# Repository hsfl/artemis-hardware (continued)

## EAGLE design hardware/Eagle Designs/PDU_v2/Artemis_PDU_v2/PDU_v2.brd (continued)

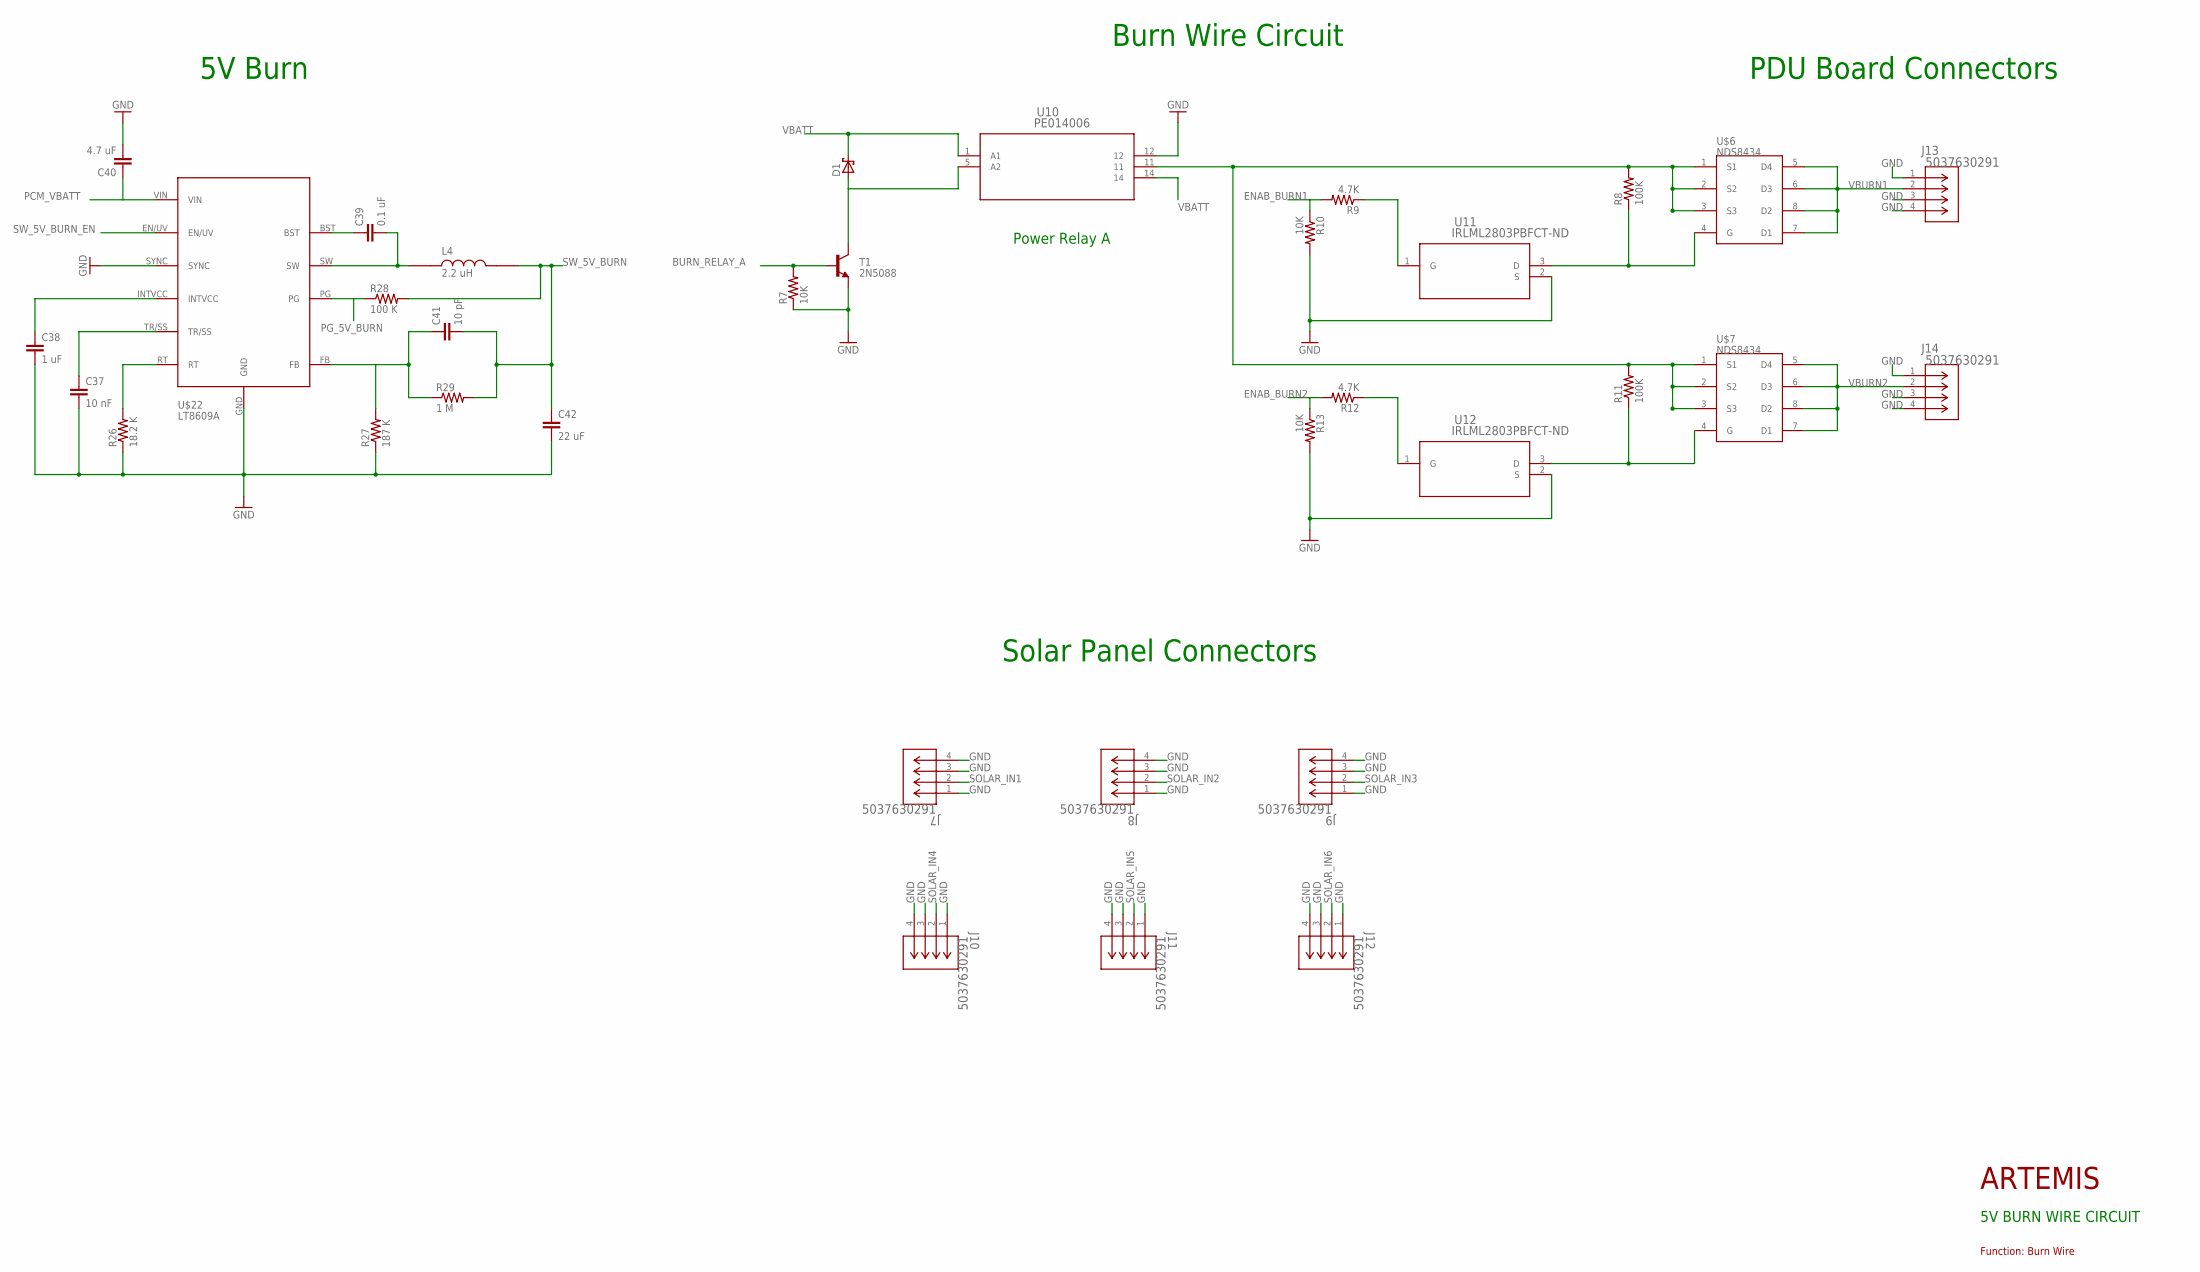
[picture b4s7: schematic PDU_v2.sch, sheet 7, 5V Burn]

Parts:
C37: 10 nF; 0805
C38: 1 uF; 0805
C39: 0.1 uF; 0805
C40: 4.7 uF; 0805
C41: 10 pF; 0805
C42: 22 uF; 1206
D1: SBR2A40P1Q7DFLS130L-7; POWERDI-123
J7, J8, J9, J10, J11, J12, J13, J14: 5037630291; CON_5037630291
L4: 2.2 uH; IND_XFL4020-222ME
R7, R10, R13: 10K; 0603-RES
R8, R11: 100K; 0603-RES
R9, R12: 4.7K; 0603-RES
R26: 18.2 K; 0805
R27: 187 K; 0805
R28: 100 K; 0805
R29: 1 M; 0805
T1: 2N5088; TO92
U10: PE014006; RELAY5-PE_CO
U11, U12: IRLML2803PBFCT-ND; PG-TO23-3_INF
U$6, U$7: NDS8434; SO08
U$22: LT8609A; MSOP_10PAD

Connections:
BURN_RELAY_A: R7.2, T1.2 (B)
ENAB_BURN1: R9.2, R10.1
ENAB_BURN2: R12.2, R13.1
GND: C37.2, C38.2, C40.2, C42.2, J7.1, J7.3, J7.4, J8.1, J8.3, J8.4, J9.1, J9.3, J9.4, J10.1, J10.3, J10.4, J11.1, J11.3, J11.4, J12.1, J12.3, J12.4, J13.1, J13.3, J13.4, J14.1, J14.3, J14.4, R7.1, R10.2, R13.2, R26.1, R27.1, T1.3 (E), U10.12, U11.2 (S), U12.2 (S), U$22.GND, U$22.SYNC; also elsewhere on the board
unnamed: R8.2, R11.2, U10.11, U$6.1 (S1), U$6.2 (S2), U$6.3 (S3), U$7.1 (S1), U$7.2 (S2), U$7.3 (S3)
unnamed: R12.1, U12.1 (G)
unnamed: R11.1, U12.3 (D), U$7.4 (G)
unnamed: D1.A, T1.1 (C), U10.5 (A2)
unnamed: R9.1, U11.1 (G)
unnamed: R8.1, U11.3 (D), U$6.4 (G)
unnamed: R26.2, U$22.RT
unnamed: C37.1, U$22.TR/SS
unnamed: C38.1, U$22.INTVCC
unnamed: C39.1, U$22.BST
unnamed: C39.2, L4.1, U$22.SW
unnamed: C41.1, R27.2, R29.1, U$22.FB
PCM_VBATT: C40.1, U$22.VIN; also elsewhere on the board
PG_5V_BURN: R28.1, U$22.PG
SOLAR_IN1: J7.2; also elsewhere on the board
SOLAR_IN2: J8.2; also elsewhere on the board
SOLAR_IN3: J9.2; also elsewhere on the board
SOLAR_IN4: J10.2; also elsewhere on the board
SOLAR_IN5: J11.2; also elsewhere on the board
SOLAR_IN6: J12.2; also elsewhere on the board
SW_5V_BURN: C41.2, C42.1, L4.2, R28.2, R29.2
SW_5V_BURN_EN: U$22.EN/UV
VBATT: D1.C, U10.1 (A1), U10.14; also elsewhere on the board
VBURN1: J13.2, U$6.5 (D4), U$6.6 (D3), U$6.7 (D1), U$6.8 (D2)
VBURN2: J14.2, U$7.5 (D4), U$7.6 (D3), U$7.7 (D1), U$7.8 (D2)

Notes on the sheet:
5V Burn
Power Relay A
Burn Wire Circuit
PDU Board Connectors
Solar Panel Connectors
ARTEMIS
5V BURN WIRE CIRCUIT
Function: Burn Wire

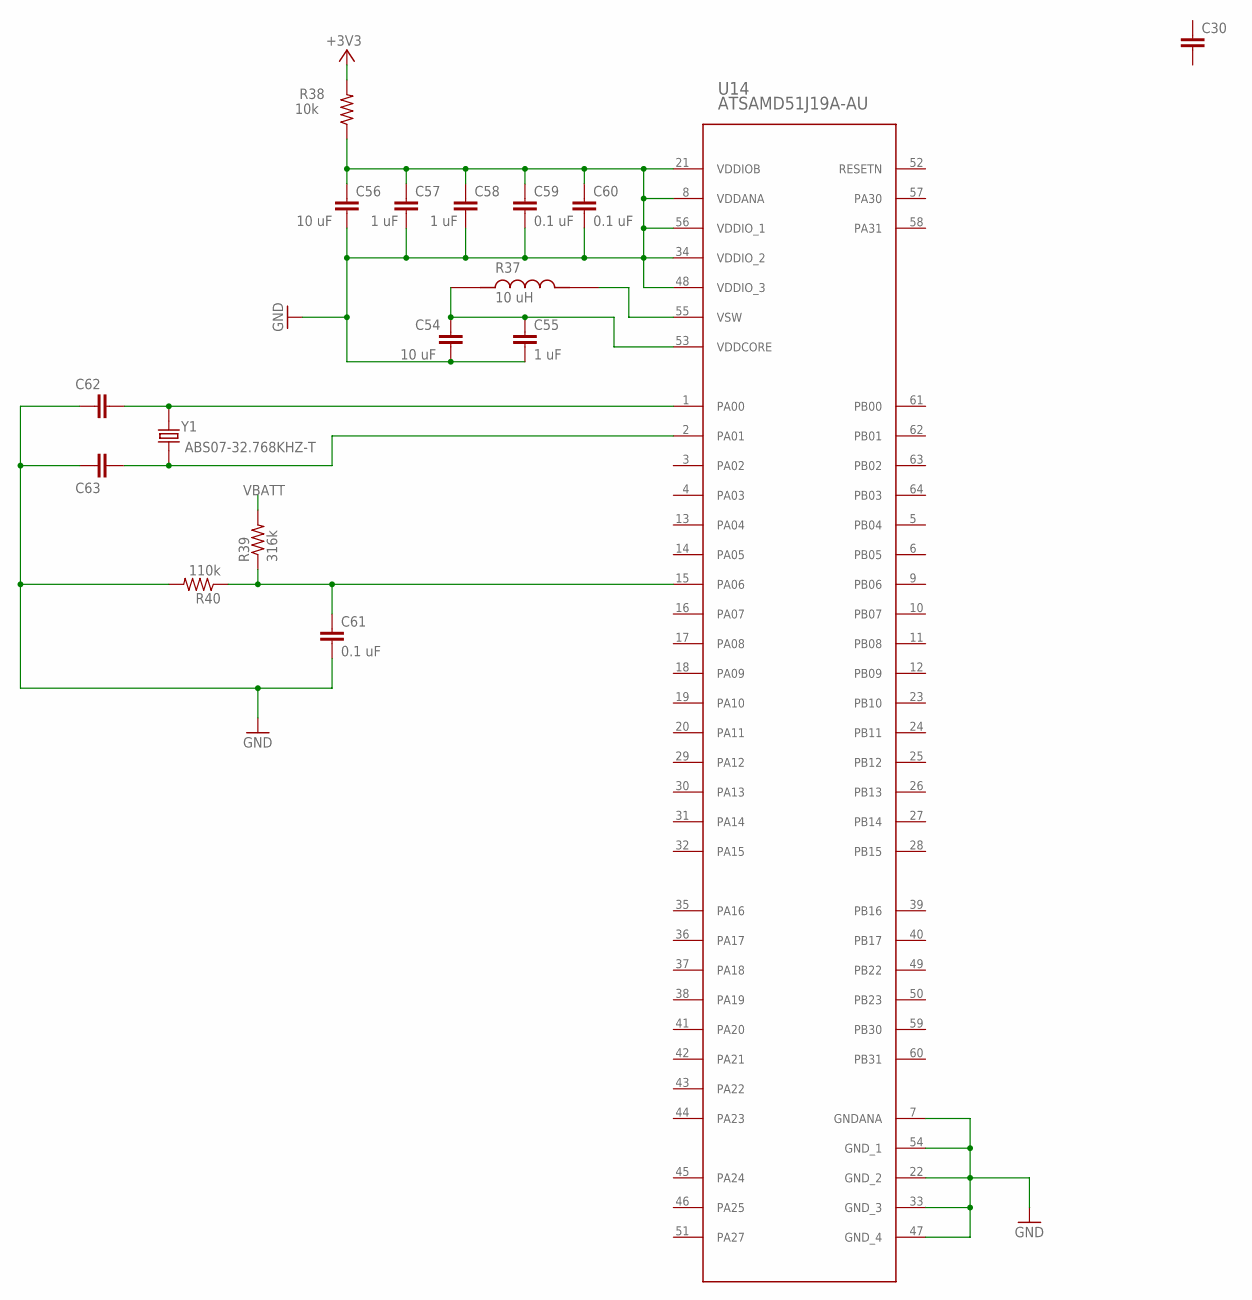
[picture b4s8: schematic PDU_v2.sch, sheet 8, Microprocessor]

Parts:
C30, C62, C63: CAP0805; 0805
C54, C56: 10 uF; 0805
C55, C57, C58: 1 uF; 0805
C59, C60, C61: 0.1 uF; 0805
R37: 10 uH; RESC0805X60N
R38: 10k; 0805
R39: 316k; 0805
R40: 110k; 0805
U14: ATSAMD51J19A-AU; TQFP64_PT_MCH
Y1: ABS07-32.768KHZ-T; XTAL_ABS07-32.768KHZ-T

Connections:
+3V3: R38.2
GND: C54.2, C55.2, C56.1, C56.2, C57.1, C57.2, C58.1, C58.2, C59.1, C59.2, C60.1, C60.2, C61.2, C62.1, C63.1, R38.1, R40.2, U14.7 (GNDANA), U14.8 (VDDANA), U14.21 (VDDIOB), U14.22 (GND_2), U14.33 (GND_3), U14.34 (VDDIO_2), U14.47 (GND_4), U14.48 (VDDIO_3), U14.54 (GND_1), U14.56 (VDDIO_1); also elsewhere on the board
unnamed: R37.2, U14.55 (VSW)
unnamed: C61.1, R39.1, R40.1, U14.15 (PA06)
unnamed: C54.1, C55.1, R37.1, U14.53 (VDDCORE)
unnamed: C62.2, U14.1 (PA00), Y1.2
unnamed: C63.2, U14.2 (PA01), Y1.1
VBATT: R39.2; also elsewhere on the board

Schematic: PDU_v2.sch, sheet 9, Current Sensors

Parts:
C29: 0.1 uF; 0805
R34: 3.3k; 0805
R35: 2m; 0805
R36: 3.3k; 0603-RES
U15: INA219BIDR; SOIC127P599X175-8N
U$2, U$4: TEST_POINT

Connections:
GND: C29.2, R35.2, U15.6 (GND), U15.7 (VIN-); also elsewhere on the board
unnamed: U15.2 (A0), U$2.1
unnamed: U15.1 (A1), U$4.1
unnamed: R34.2, U15.3 (SDA)
unnamed: R36.2, U15.4 (SCL)
VCC: R35.1, U15.8 (VIN+); also elsewhere on the board
VS: C29.1, R34.1, R36.1, U15.5 (VS)

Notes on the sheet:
ARTEMIS
Current Sensor
Function: Current shunt, Power Monitor
*VS = Voltage Source -> In this case, Solar Panel

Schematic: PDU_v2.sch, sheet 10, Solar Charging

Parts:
U$1: MP2639A; QFN26-4X4_MP2639A

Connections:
AGND: U$1.10 (AGND)
BST: U$1.6 (BST)
LX: U$1.2 (LX)
PGND: U$1.5 (PGND)
SW: U$1.4 (SW)
VCC: U$1.9 (VCC); also elsewhere on the board
VH: U$1.3 (VH)
VL: U$1.1 (VL)

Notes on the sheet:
Solar Charging Function
ARTEMIS
Function: Solar Charging
Solar Chargion Region

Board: 2 copper layers, 170 parts (0 on the bottom side), 96 nets, no tracks yet.
